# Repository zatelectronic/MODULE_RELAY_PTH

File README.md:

<div align="center">

# MODULE RELAY

**Módulo de relé isolado com acionamento por nível alto (High Level Trigger), componentes totalmente através-furo (PTH), isolação óptica e relé de potência 12VDC / 15A**

</div>

---

## 📋 Índice

- [MODULE RELAY](#module-relay)
  - [📋 Índice](#-índice)
  - [Visão Geral](#visão-geral)
  - [Imagens do Projeto](#imagens-do-projeto)
  - [Diferenças em relação ao MODULE RELAY SMD](#diferenças-em-relação-ao-module-relay-smd)
  - [Funcionalidades](#funcionalidades)
  - [Diagrama de Funcionamento](#diagrama-de-funcionamento)
  - [Especificações Técnicas](#especificações-técnicas)
  - [Lista de Materiais](#lista-de-materiais)
  - [Pinagem dos Conectores](#pinagem-dos-conectores)
    - [J1 — Entrada (Controle)](#j1--entrada-controle)
    - [J2 — Saída (Carga)](#j2--saída-carga)
  - [Aplicações](#aplicações)
  - [Estrutura do Repositório](#estrutura-do-repositório)
  - [Como Usar](#como-usar)
    - [Conexão básica com Arduino / ESP32](#conexão-básica-com-arduino--esp32)
    - [Exemplo de código Arduino](#exemplo-de-código-arduino)
    - [Dica de Montagem](#dica-de-montagem)
  - [⚠️ Avisos de Segurança](#️-avisos-de-segurança)
  - [Sobre](#sobre)

---

## Visão Geral

**MODULE RELAY** é um módulo de acionamento de relé com **isolação galvânica total** entre o circuito de controle e a carga, projetado pela **ZAT ELECTRONIC** utilizando **KiCad 10**. Diferente da versão SMD, esta placa utiliza exclusivamente **componentes através-furo (PTH)**, tornando-a ideal para montagem manual, prototipagem e laboratórios maker.

O circuito utiliza o optoacoplador **PC817** (DIP-4 PTH) para isolar eletricamente o sinal de controle (proveniente de microcontroladores como Arduino, ESP32, etc.) do circuito de potência. O transistor **BC548** (TO-92 PTH) aciona a bobina do relé de potência 12VDC, capaz de comutar cargas de até **15A em 125VAC ou 24VDC**.

> ⚡ **High Level Trigger** — o relé é acionado com sinal lógico alto (+3,3V ou +5V) no pino de entrada, com proteção por isolação óptica para máxima segurança do microcontrolador.

---

## Imagens do Projeto

<div align="center">

*Vista superior — relé de potência, optoacoplador PC817 DIP, transistor BC548 e bornes KRE*

<br/>

*Vista isométrica — componentes PTH, LED azul 5mm e layout geral da placa*

<br/>

<br/>

<br/>

</div>

---

## Diferenças em relação ao MODULE RELAY SMD

| Característica | MODULE RELAY (PTH) | MODULE RELAY SMD |
|----------------|-------------------|-----------------|
| **Tipo de montagem** | Através-furo (PTH) | Montagem superficial (SMD) |
| **Optoacoplador** | PC817 DIP-4 PTH | PC817S SOP-4 SMD |
| **Transistor driver** | BC548 (TO-92 PTH) | MMBT2222A-TP (SOT-23 SMD) |
| **Resistores** | Axial 0,5W PTH | SMD 0805 |
| **LED de status** | 5mm PTH azul | SMD 0805 |
| **Diodo de roda livre** | 1N4007 PTH axial | 1N4007 SMA SMD |
| **Facilidade de montagem** | Alta — soldagem manual simples | Requer soldagem SMD |
| **Público alvo** | Iniciantes, makers, laboratório | Produção, compacto, profissional |

---

## Funcionalidades

- ✅ **Relé de potência 12VDC / 15A** — contatos SPDT (NO, COM, NC), 15A 125VAC / 15A 24VDC
- ✅ **Isolação óptica via PC817** (DIP-4 PTH) — proteção galvânica total entre controle e carga
- ✅ **Transistor BC548** (TO-92 PTH) — driver NPN para acionamento da bobina
- ✅ **Diodo de roda livre 1N4007** (PTH axial) — proteção contra tensão reversa da bobina
- ✅ **LED azul 5mm PTH** — indicação visual de relé acionado
- ✅ **High Level Trigger** — compatível com 3,3V e 5V (Arduino, ESP32, Raspberry Pi, etc.)
- ✅ **Bornes KRE parafuso** (3 pinos, passo 5,0mm) — conexão robusta para entrada e saída
- ✅ **Todos os componentes PTH** — montagem manual fácil, ideal para prototipagem
- ✅ **Made in Brazil** — serigrafia na PCB

---

## Diagrama de Funcionamento

```
Microcontrolador / Sinal de Controle
        │
    +IN ●──[R1 220Ω]──► PC817 (LED interno)
    GND ●──────────────► PC817 (GND interno)
                               │
                         (Isolação óptica)
                               │
                         PC817 (Transistor)
                               │
              +12V ──[R4 470Ω]──► LED L1 (status azul)
              +12V ──[R3 4,7KΩ]──► Base BC548 (Q1)
                               │
                        [R2 10KΩ] pull-down (Base→GND)
                               │
                        Coletor BC548 (Q1)
                               │
                    Bobina K1 (Relé 12VDC)
                               │
                        [D1 1N4007] ← Flyback
                               │
                        GND ───┘

              Contatos do Relé (J2 — OUT)
         ┌────────────────────────────────┐
         │   NO  │  COMUM  │  NC          │
         └────────────────────────────────┘
          Carga: até 15A / 125VAC ou 24VDC
```

---

## Especificações Técnicas

| Parâmetro | Valor |
|-----------|-------|
| **Relé** | 12VDC / SPDT (Form C) |
| **Tensão da Bobina** | 12VDC |
| **Corrente máx. de carga (AC)** | 15A @ 125VAC |
| **Corrente máx. de carga (DC)** | 15A @ 24VDC |
| **Tipo de contato** | SPDT — NO, NC, COM |
| **Tensão de alimentação do módulo** | +12V |
| **Tensão de controle (sinal IN)** | 3,3V a 5V (High Level Trigger) |
| **Isolação** | Óptica — PC817 DIP-4 |
| **Transistor driver** | BC548 (TO-92, NPN) |
| **Diodo de proteção** | 1N4007 (PTH axial) |
| **LED de status** | 5mm PTH azul |
| **Resistores** | Axial 0,5W PTH |
| **Conectores** | Borne KRE parafuso 3 pinos, passo 5,0mm |
| **Ferramenta de Projeto** | KiCad 10 |
| **Tipo de montagem** | PTH — Através-furo |

---

## Lista de Materiais

| Ref | Componente | Valor / Parte | Encapsulamento |
|-----|-----------|--------------|----------------|
| K1 | Relé de Potência | 12VDC / 15A SPDT | PTH |
| U1 | Optoacoplador | PC817 | DIP-4 PTH |
| Q1 | Transistor NPN | BC548 | TO-92 PTH |
| D1 | Diodo de Roda Livre | 1N4007 | PTH Axial |
| L1 | LED de Status | LED 5mm Azul | PTH 5mm |
| R1 | Resistor de entrada (opto) | 220Ω | Axial 0,5W PTH |
| R2 | Resistor pull-down (base) | 10KΩ | Axial 0,5W PTH |
| R3 | Resistor de base (transistor) | 4,7KΩ | Axial 0,5W PTH |
| R4 | Resistor de LED | 470Ω | Axial 0,5W PTH |
| J1 | Borne de Entrada (Controle) | +12V, +IN, GND | KRE 3 pinos 5,0mm |
| J2 | Borne de Saída (Carga) | NO, COM, NC | KRE 3 pinos 5,0mm |

---

## Pinagem dos Conectores

### J1 — Entrada (Controle)

| Pino | Sinal | Descrição |
|------|-------|-----------|
| 1 | +12V | Alimentação da bobina do relé |
| 2 | +IN | Sinal de controle (3,3V–5V = relé ON) |
| 3 | GND | Terra comum |

### J2 — Saída (Carga)

| Pino | Sinal | Descrição |
|------|-------|-----------|
| 1 | NO | Normalmente aberto (fecha quando acionado) |
| 2 | COM | Terminal comum do relé |
| 3 | NC | Normalmente fechado (abre quando acionado) |

---

## Aplicações

- 🏠 **Automação residencial** — acionamento de lâmpadas, tomadas e ventiladores
- 🤖 **Projetos com Arduino e ESP32** — controle de cargas AC com isolação galvânica
- 🏫 **Ensino e prototipagem** — componentes PTH facilmente soldáveis e substituíveis
- 💡 **Controle de iluminação** — painéis de LED de alta potência e luminárias
- 🔌 **Proteção de circuitos** — isolação entre lógica de baixa tensão e rede elétrica
- 📡 **IoT e domótica** — integração com sistemas MQTT, Home Assistant, etc.

---

## Estrutura do Repositório

```
MODULE_RELAY/
├── MODULE_RELAY.kicad_pro        # Arquivo de projeto KiCad
├── MODULE_RELAY.kicad_sch        # Esquemático (KiCad 10)
├── MODULE_RELAY.kicad_pcb        # Layout da PCB (KiCad 10)
├── MODULE_RELAY.kicad_prl        # Configurações locais do projeto
├── packages3D/                   # Modelos 3D arquivados (STEP / WRL)
│   ├── PC817_DIP.step
│   ├── Relé_12VDC_15A.STEP
│   ├── DG306-5.0-03P-12-00AH.STEP
│   ├── Transistor BC548.STEP
│   ├── Diodo 1N4007.STEP
│   ├── LED 5mm Blue.step
│   └── Resistor Axial 0.5W *.STEP
├── fp-info-cache                 # Cache de footprints
├── imagem_1.png                  # Render 3D superior
├── imagem_2.png                  # Render 3D isométrico
└── README.md
```

---

## Como Usar

### Conexão básica com Arduino / ESP32

```
Arduino / ESP32             MODULE RELAY
───────────────────         ─────────────────
GND              ────────►  J1 - GND
Pino digital     ────────►  J1 - +IN

Fonte 12VDC (+)  ────────►  J1 - +12V
Fonte 12VDC (-)  ────────►  J1 - GND

Carga AC/DC      ────────►  J2 - COM + NO (ou NC)
```

### Exemplo de código Arduino

```cpp
#define RELAY_PIN 7

void setup() {
  pinMode(RELAY_PIN, OUTPUT);
  digitalWrite(RELAY_PIN, LOW); // relé desligado na inicialização
}

void loop() {
  digitalWrite(RELAY_PIN, HIGH); // aciona o relé
  delay(1000);
  digitalWrite(RELAY_PIN, LOW);  // desaciona o relé
  delay(1000);
}
```

### Dica de Montagem

> 🔧 Por ser totalmente PTH, recomenda-se a seguinte ordem de soldagem: resistores primeiro, depois diodo, transistor BC548, optoacoplador PC817, LED, relé e por último os bornes KRE.

## ⚠️ Avisos de Segurança

> 🔴 **ATENÇÃO — TENSÕES PERIGOSAS**

- Este módulo pode comutar tensões de **rede elétrica (110V / 220V AC)**. Manuseie com extremo cuidado.
- **Nunca toque nos terminais J2 (OUT)** enquanto houver carga CA conectada e o circuito energizado.
- Utilize **caixa de proteção** adequada quando instalar em ambientes com acesso de pessoas.
- Respeite a **corrente máxima de 15A** nos contatos do relé.
- A isolação óptica protege o microcontrolador, mas **não substitui normas de segurança elétrica**.
- Projeto destinado a **profissionais e experimentadores experientes**.

---

## Sobre

<div align="center">

Projetado por **ZAT ELECTRONIC**

*MODULE RELAY — Made in Brazil 🇧🇷*

</div>>

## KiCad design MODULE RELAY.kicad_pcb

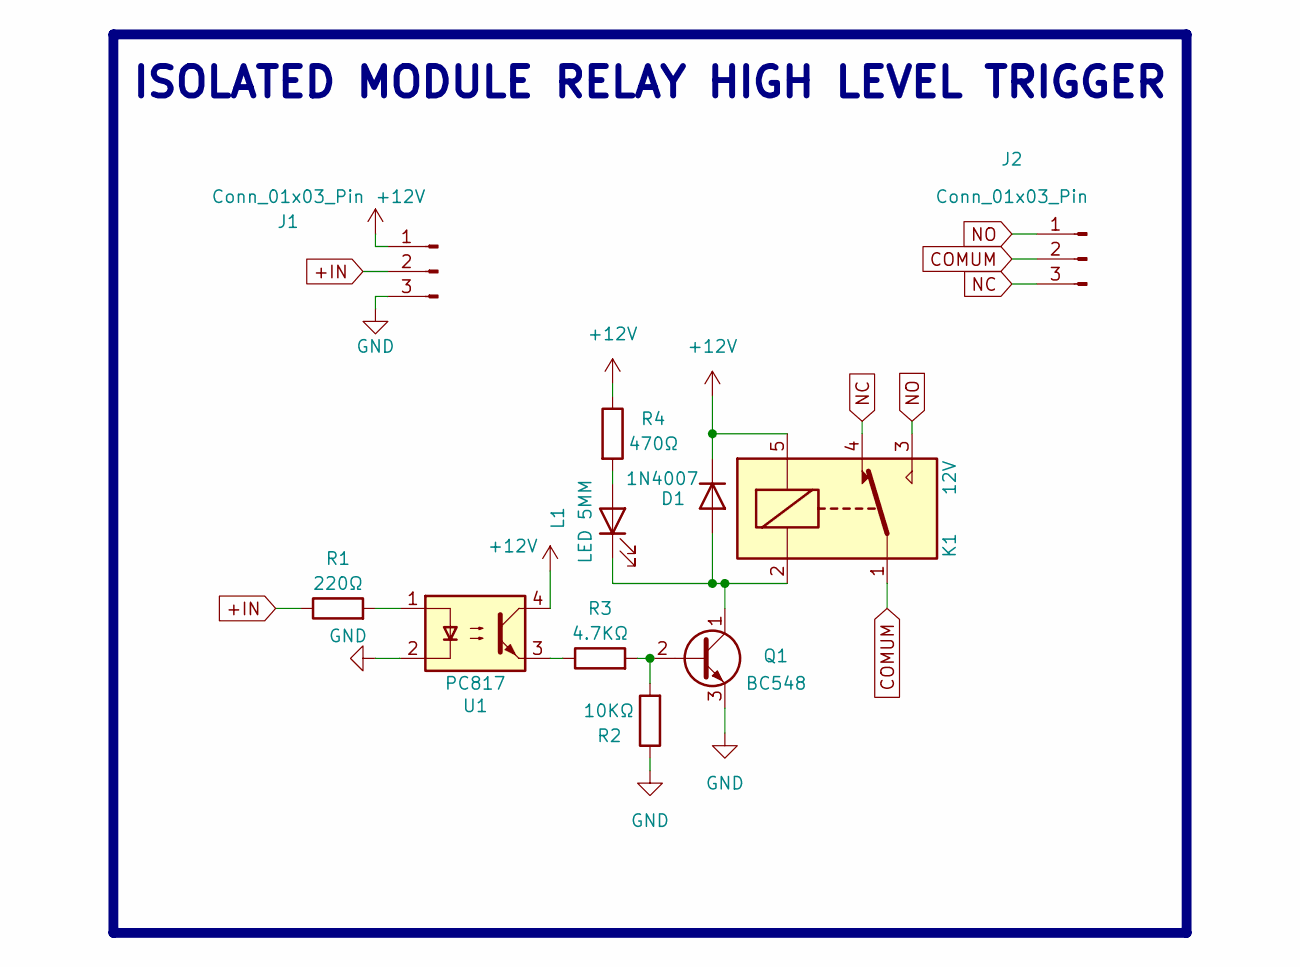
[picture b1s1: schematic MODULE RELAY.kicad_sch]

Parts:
D1: 1N4007; D_DO-41_SOD81_P10.16mm_Horizontal
J1, J2: Conn_01x03_Pin; TerminalBlock_MaiXu_MX126-5.0-03P_1x03_P5.00mm
K1: 12V; Relay_SPDT_SANYOU_SRD_Series_Form_C
L1: LED 5MM; LED_D5.0mm
Q1: BC548; TO-92_HandSolder
R1: 220Ω; R_Axial_DIN0204_L3.6mm_D1.6mm_P7.62mm_Horizontal
R2: 10KΩ; R_Axial_DIN0204_L3.6mm_D1.6mm_P7.62mm_Horizontal
R3: 4.7KΩ; R_Axial_DIN0204_L3.6mm_D1.6mm_P7.62mm_Horizontal
R4: 470Ω; R_Axial_DIN0204_L3.6mm_D1.6mm_P7.62mm_Horizontal
U1: PC817; DIP-4_W7.62mm_LongPads

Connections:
+12V: D1.1 (K), J1.1, K1.5, R4.1, U1.4
+IN: J1.2, R1.1
COMUM: J2.2, K1.1
GND: J1.3, Q1.3 (E), R2.1, U1.2
NC: J2.3, K1.4
NO: J2.1, K1.3
unnamed: D1.2 (A), K1.2, L1.1 (K), Q1.1 (C)
unnamed: L1.2 (A), R4.2
unnamed: Q1.2 (B), R2.2, R3.2
unnamed: R1.2, U1.1
unnamed: R3.1, U1.3

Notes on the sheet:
ISOLATED MODULE RELAY HIGH LEVEL TRIGGER

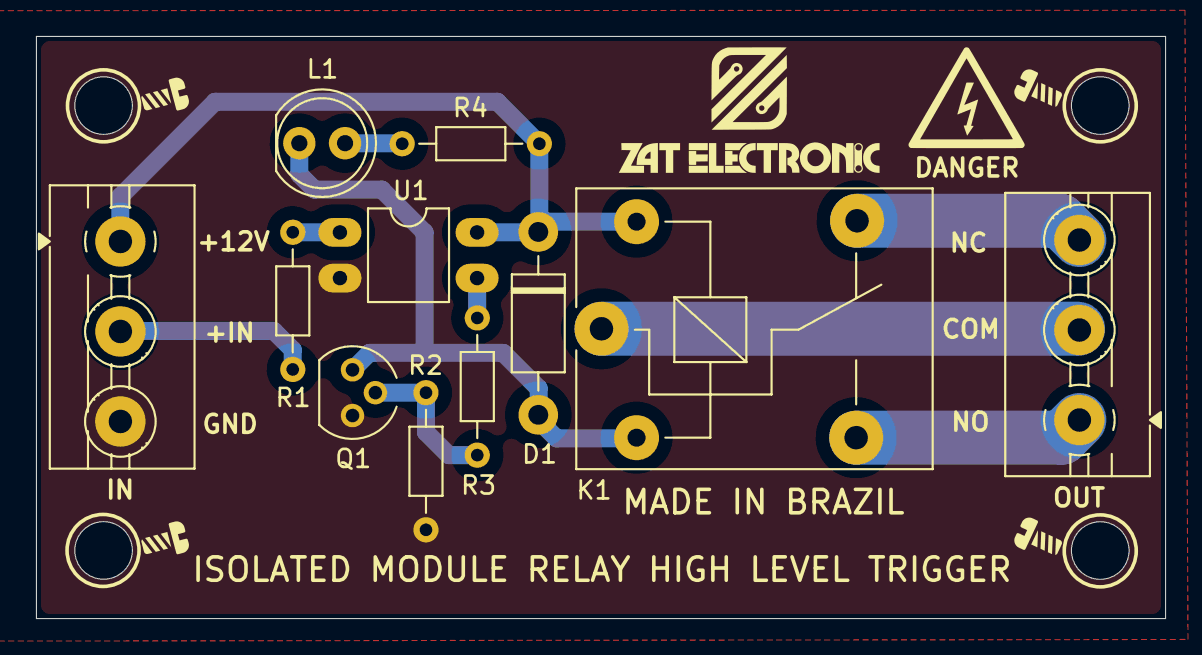
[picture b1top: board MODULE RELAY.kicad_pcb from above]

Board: 2 copper layers, 62.7 x 32.3 mm, 11 parts (0 on the bottom side), 11 nets.

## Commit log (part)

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2026-06-28 commit_3
2026-06-29 COMMIT-4
2026-06-29 COMMIT-5
